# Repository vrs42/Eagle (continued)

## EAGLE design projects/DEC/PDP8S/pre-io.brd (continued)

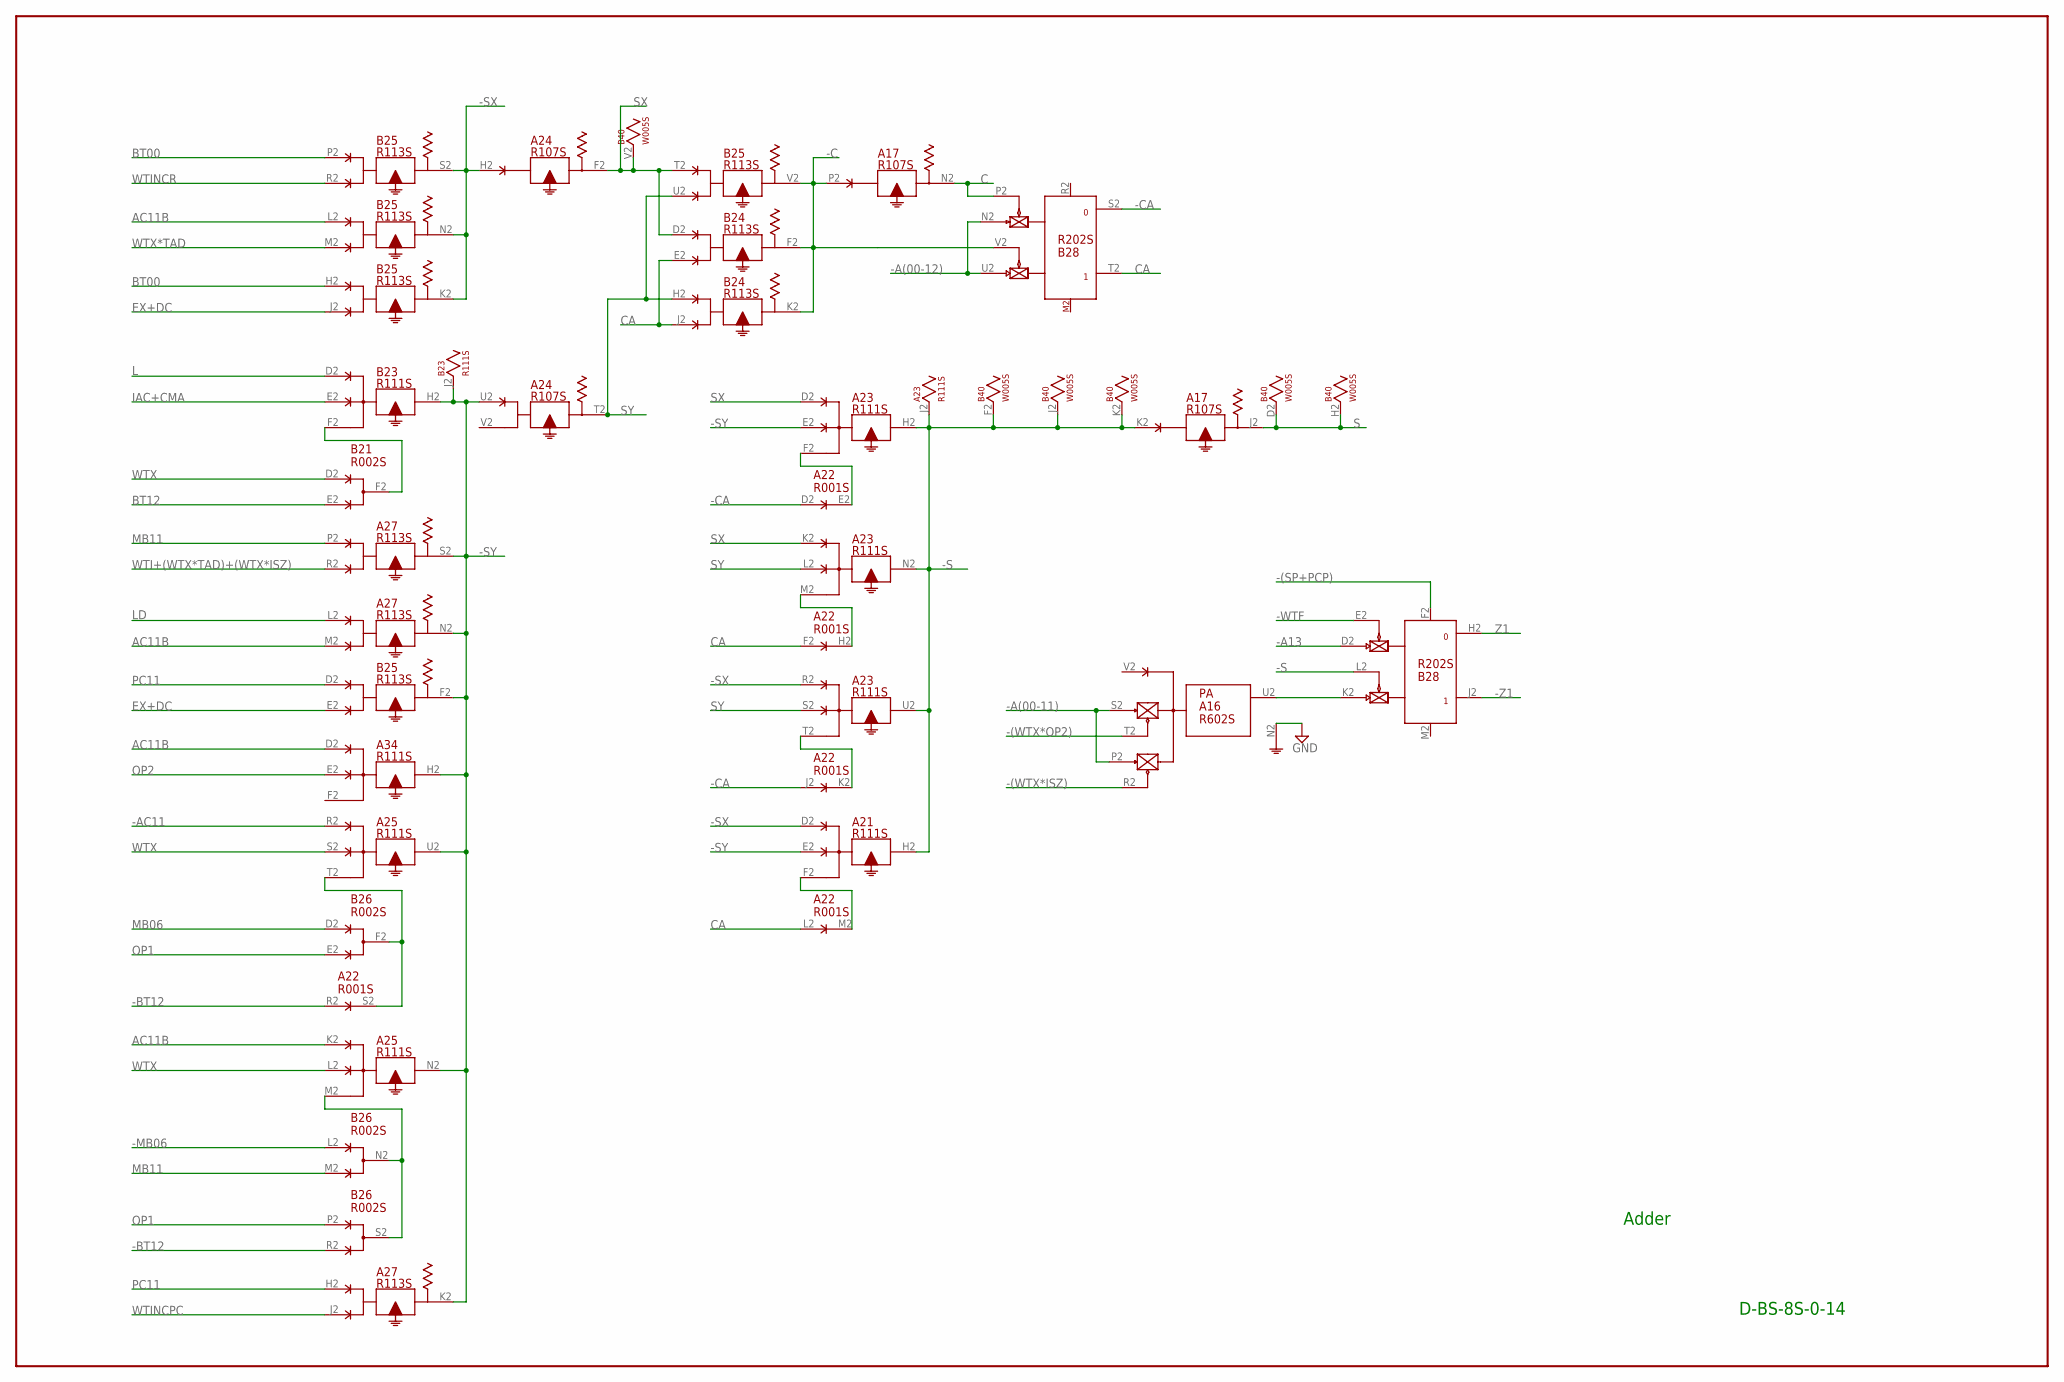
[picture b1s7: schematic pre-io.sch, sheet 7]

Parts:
A16: R602S; H807S
A17, A24: R107S; H807S
A21, A23, A25, A34: R111S; H807S
A22: R001S; H807S
A27: R113S; H807S
B21, B26: R002S; H807S
B23: R111S; H807S
B24, B25: R113S; H807S
B28: R202S; H807S
B40: W005S; H807S

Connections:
-15V: A16.B2 (-15V), A17.B2 (-15V), A21.B2 (-15V), A22.B2 (-15V), A23.B2 (-15V), A24.B2 (-15V), A25.B2 (-15V), A27.B2 (-15V), A34.B2 (-15V), B21.B2 (-15V), B23.B2 (-15V), B24.B2 (-15V), B25.B2 (-15V), B26.B2 (-15V), B28.B2 (-15V), B40.B2 (-15V); also elsewhere on the board
-(SP+PCP): B28.F2 (RESET); also elsewhere on the board
-(WTX*ISZ): A16.R2 (F); also elsewhere on the board
-(WTX*OP2): A16.T2 (J); also elsewhere on the board
-A13: B28.D2 (PU0); also elsewhere on the board
-A(00-11): A16.P2 (E), A16.S2 (H); also elsewhere on the board
-A(00-12): B28.N2 (PU0), B28.U2 (PU1); also elsewhere on the board
-AC11: A25.R2
-BT12: A22.R2 (D), B26.R2 (E); also elsewhere on the board
-C: A17.P2, B24.F2, B24.K2, B25.V2, B28.V2 (EN1)
-CA: A22.D2 (D), A22.J2 (D), B28.S2 (0)
-MB06: B26.L2 (D); also elsewhere on the board
-S: A17.K2, A21.H2, A23.H2, A23.J2, A23.N2, A23.U2, B28.L2 (EN1), B40.F2, B40.J2, B40.K2
-SX: A21.D2, A23.R2, A24.H2, B25.K2, B25.N2, B25.S2
-SY: A21.E2, A23.E2, A24.U2, A25.N2, A25.U2, A27.K2, A27.N2, A27.S2, A34.H2, B23.H2, B23.J2, B25.F2
-WTF: B28.E2 (EN0); also elsewhere on the board
-Z1: B28.J2 (1)
AC11B: A25.K2, A27.M2, A34.D2, B25.L2; also elsewhere on the board
BT00: B25.H2, B25.P2; also elsewhere on the board
BT12: B21.E2 (E)
C: A17.N2, B28.P2 (EN0)
CA: A22.F2 (D), A22.L2 (D), B24.E2, B24.J2, B28.T2 (1)
EX+DC: B25.E2, B25.J2; also elsewhere on the board
GND: A16.C2 (GND), A16.N2 (C), A17.C2 (GND), A21.C2 (GND), A22.C2 (GND), A23.C2 (GND), A24.C2 (GND), A25.C2 (GND), A27.C2 (GND), A34.C2 (GND), B21.C2 (GND), B23.C2 (GND), B24.C2 (GND), B25.C2 (GND), B26.C2 (GND), B28.C2 (GND), B40.C2 (GND); also elsewhere on the board
IAC+CMA: B23.E2; also elsewhere on the board
L: B23.D2; also elsewhere on the board
LD: A27.L2; also elsewhere on the board
MB06: B26.D2 (D); also elsewhere on the board
MB11: A27.P2, B26.M2 (E); also elsewhere on the board
unnamed: B21.F2 (F), B23.F2
unnamed: A16.U2 (K), B28.K2 (PU1)
unnamed: A22.S2 (E), A25.T2, B26.F2 (F)
unnamed: A22.E2 (E), A23.F2
unnamed: A25.M2, B26.N2 (F), B26.S2 (F)
unnamed: A22.H2 (E), A23.M2
unnamed: A22.K2 (E), A23.T2
unnamed: A21.F2, A22.M2 (E)
OP1: B26.E2 (E), B26.P2 (D); also elsewhere on the board
OP2: A34.E2; also elsewhere on the board
PC11: A27.H2, B25.D2; also elsewhere on the board
S: A17.J2, B40.D2, B40.H2; also elsewhere on the board
SX: A23.D2, A23.K2, A24.F2, B24.D2, B25.T2, B40.V2
SY: A23.L2, A23.S2, A24.T2, B24.H2, B25.U2
VCC: A16.A2 (VCC), A17.A2 (VCC), A21.A2 (VCC), A22.A2 (VCC), A23.A2 (VCC), A24.A2 (VCC), A25.A2 (VCC), A27.A2 (VCC), A34.A2 (VCC), B21.A2 (VCC), B23.A2 (VCC), B24.A2 (VCC), B25.A2 (VCC), B26.A2 (VCC), B28.A2 (VCC), B40.A2 (VCC); also elsewhere on the board
WTI+(WTX*TAD)+(WTX*ISZ): A27.R2; also elsewhere on the board
WTINCPC: A27.J2
WTINCR: B25.R2
WTX: A25.L2, A25.S2, B21.D2 (D); also elsewhere on the board
WTX*TAD: B25.M2; also elsewhere on the board
Z1: B28.H2 (0); also elsewhere on the board

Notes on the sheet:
D-BS-8S-0-14
Adder

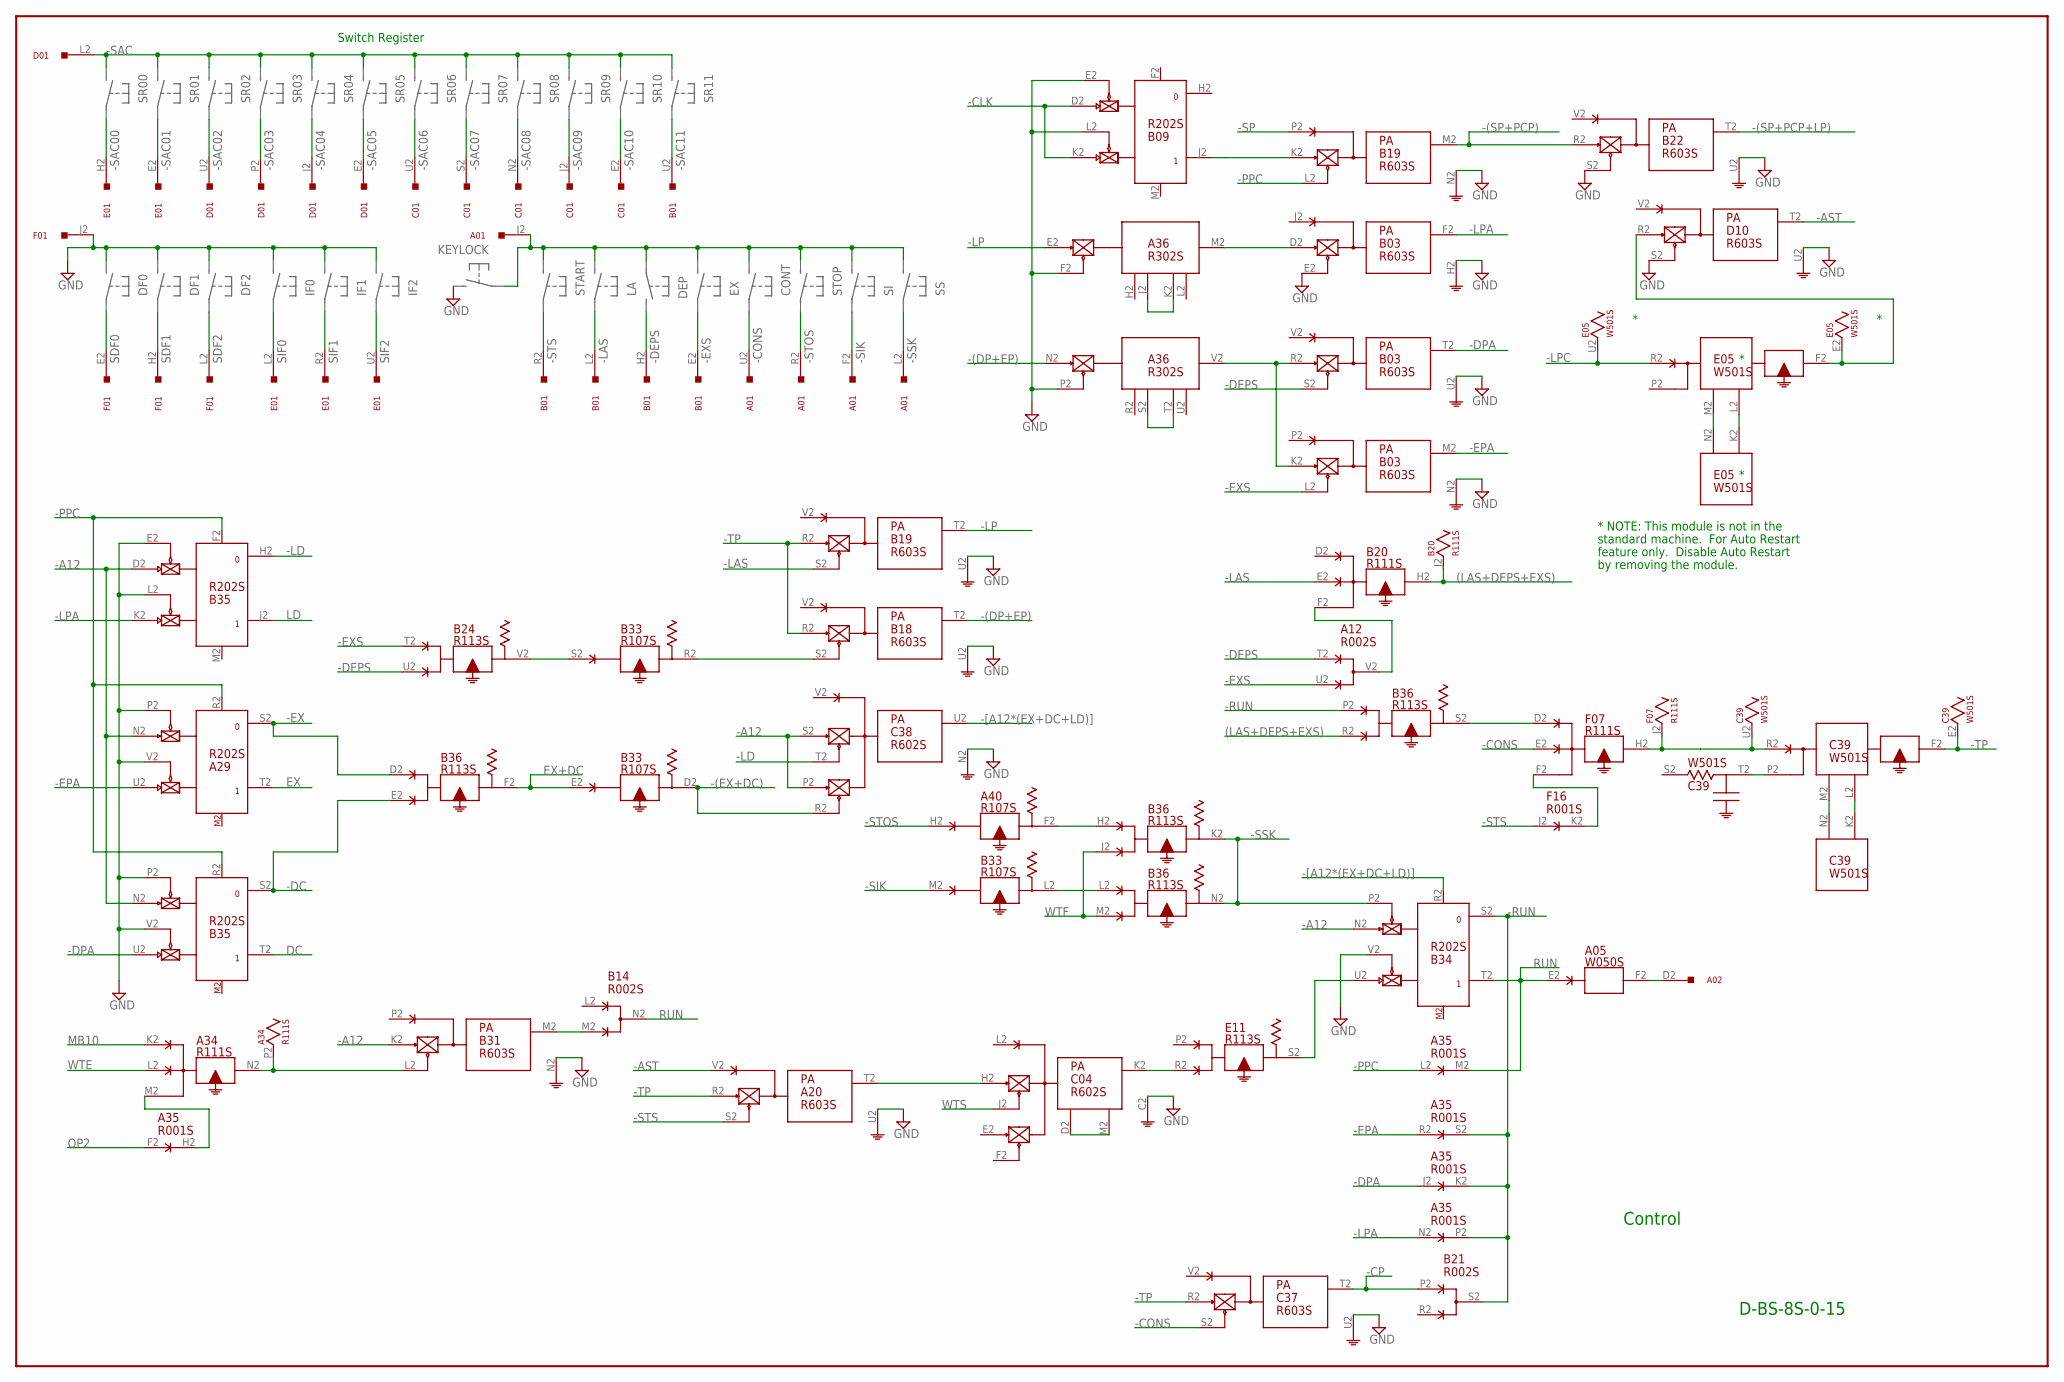
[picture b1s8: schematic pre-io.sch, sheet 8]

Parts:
A01, A02: W023S; H807S
A05: W050S; H807S
A12: R002S; H807S
A20: R603S; H807S
A29: R202S; H807S
A34: R111S; H807S
A35: R001S; H807S
A36: R302S; H807S
A40: R107S; H807S
B01: W023S; H807S
B03, B18, B19, B22, B31: R603S; H807S
B09, B34, B35: R202S; H807S
B14, B21: R002S; H807S
B20: R111S; H807S
B24, B36: R113S; H807S
B33: R107S; H807S
C01: W023S; H807S
C04, C38: R602S; H807S
C37: R603S; H807S
C39: W501S; H807S
D01: W023S; H807S
D10: R603S; H807S
E01: W023S; H807S
E05: W501S; H807S
E11: R113S; H807S
F01: W023S; H807S
F07: R111S; H807S
F16: R001S; H807S

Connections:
(LAS+DEPS+EXS): B20.H2, B20.J2, B36.R2
-15V: A05.B2 (-15V), A12.B2 (-15V), A20.B2 (-15V), A29.B2 (-15V), A34.B2 (-15V), A35.B2 (-15V), A36.B2 (-15V), A40.B2 (-15V), B03.B2 (-15V), B09.B2 (-15V), B14.B2 (-15V), B18.B2 (-15V), B19.B2 (-15V), B20.B2 (-15V), B21.B2 (-15V), B22.B2 (-15V), B24.B2 (-15V), B31.B2 (-15V), B33.B2 (-15V), B34.B2 (-15V), B35.B2 (-15V), B36.B2 (-15V), C04.B2 (-15V), C37.B2 (-15V), C38.B2 (-15V), C39.B2 (-15V), D10.B2 (-15V), E05.B2 (-15V), E11.B2 (-15V), F07.B2 (-15V), F16.B2 (-15V); also elsewhere on the board
-(DP+EP): A36.N2 (E), B18.T2 (O); also elsewhere on the board
-(EX+DC): B33.D2, C38.R2 (F); also elsewhere on the board
-(SP+PCP): B19.M2 (O), B22.R2 (PU0); also elsewhere on the board
-(SP+PCP+LP): B22.T2 (O); also elsewhere on the board
-A12: A29.N2 (PU0), B31.K2 (PU0), B34.N2 (PU0), B35.D2 (PU0), B35.N2 (PU0), C38.P2 (E), C38.S2 (H); also elsewhere on the board
-AST: A20.V2, D10.T2 (O)
-CLK: B09.D2 (PU0), B09.K2 (PU1)
-CONS: A01.U2, C37.S2 (EN0), F07.E2
-CP: B21.P2 (D), C37.T2 (O)
-DC: B35.S2 (0), B36.E2; also elsewhere on the board
-DEPS: A12.T2 (D), B01.H2, B03.S2 (EN0), B24.U2
-DPA: A35.J2 (D), B03.T2 (O), B35.U2 (PU1); also elsewhere on the board
-EPA: A29.U2 (PU1), A35.R2 (D), B03.M2 (O); also elsewhere on the board
-EX: A29.S2 (0), B36.D2; also elsewhere on the board
-EXS: A12.U2 (E), B01.E2, B03.L2 (EN0), B24.T2
-LAS: B01.L2, B19.S2 (EN0), B20.E2
-LD: B35.H2 (0), C38.T2 (J); also elsewhere on the board
-LP: A36.E2 (E), B19.T2 (O); also elsewhere on the board
-LPA: A35.N2 (D), B03.F2 (O), B35.K2 (PU1); also elsewhere on the board
-LPC: E05.R2 (R), E05.U2
-PPC: A29.R2 (RESET), A35.L2 (D), B19.L2 (EN0), B35.F2 (RESET), B35.R2 (RESET); also elsewhere on the board
-RUN: A35.K2 (E), A35.P2 (E), A35.S2 (E), B21.S2 (F), B34.S2 (0), B36.P2; also elsewhere on the board
-SAC: D01.L2; also elsewhere on the board
-SAC00: E01.H2
-SAC01: E01.E2
-SAC02: D01.U2
-SAC03: D01.P2
-SAC04: D01.J2
-SAC05: D01.E2
-SAC06: C01.U2
-SAC07: C01.S2
-SAC08: C01.N2
-SAC09: C01.J2
-SAC10: C01.E2
-SAC11: B01.U2
-SIK: A01.F2, B33.M2
-SP: B19.P2; also elsewhere on the board
-SSK: A01.L2, B34.P2 (EN0), B36.K2, B36.N2
-STOS: A01.R2, A40.H2
-STS: A20.S2 (EN0), B01.R2, F16.J2 (D)
-TP: A20.R2 (PU0), B18.R2 (PU0), B19.R2 (PU0), C37.R2 (PU0), C39.E2, C39.F2 (F)
-[A12*(EX+DC+LD)]: B34.R2 (RESET), C38.U2 (K); also elsewhere on the board
DC: B35.T2 (1); also elsewhere on the board
EX: A29.T2 (1)
EX+DC: B33.E2, B36.F2; also elsewhere on the board
GND: A05.C2 (GND), A12.C2 (GND), A20.C2 (GND), A20.U2 (G), A29.C2 (GND), A29.P2 (EN0), A29.V2 (EN1), A34.C2 (GND), A35.C2 (GND), A36.C2 (GND), A36.F2 (F), A36.P2 (F), A40.C2 (GND), B03.C2 (GND), B03.E2 (EN0), B03.H2 (G), B03.N2 (G), B03.U2 (G), B09.C2 (GND), B09.E2 (EN0), B09.L2 (EN1), B14.C2 (GND), B18.C2 (GND), B18.U2 (G), B19.C2 (GND), B19.N2 (G), B19.U2 (G), B20.C2 (GND), B21.C2 (GND), B22.C2 (GND), B22.S2 (EN0), B22.U2 (G), B24.C2 (GND), B31.C2 (GND), B31.N2 (G), B33.C2 (GND), B34.C2 (GND), B34.V2 (EN1), B35.C2 (GND), B35.E2 (EN0), B35.L2 (EN1), B35.P2 (EN0), B35.V2 (EN1), B36.C2 (GND), C04.C2 (GND), C37.C2 (GND), C37.U2 (G), C38.C2 (GND), C38.N2 (C), C39.C2 (GND), C39.V2 (GND), D10.C2 (GND), D10.S2 (EN0), D10.U2 (G), E05.C2 (GND), E05.V2 (GND), E11.C2 (GND), F01.J2, F07.C2 (GND), F16.C2 (GND); also elsewhere on the board
LD: B35.J2 (1); also elsewhere on the board
MB10: A34.K2; also elsewhere on the board
unnamed: A34.M2, A35.H2 (E)
unnamed: A34.N2, A34.P2, B31.L2 (EN0)
unnamed: B14.M2 (E), B31.M2 (O)
unnamed: B24.V2, B33.S2
unnamed: B34.U2 (PU1), E11.S2
unnamed: B18.S2 (EN0), B33.R2
unnamed: A36.S2 (J), A36.T2 (K)
unnamed: A36.J2 (J), A36.K2 (K)
unnamed: E05.M2 (M), E05.N2 (N)
unnamed: E05.K2 (K), E05.L2 (L)
unnamed: B09.J2 (1), B19.K2 (PU0)
unnamed: D10.R2 (PU0), E05.E2, E05.F2 (F)
unnamed: A36.M2 (M), B03.D2 (PU0)
unnamed: A36.V2 (M), B03.K2 (PU0), B03.R2 (PU0)
unnamed: A12.V2 (F), B20.F2
unnamed: C39.M2 (M), C39.N2 (N)
unnamed: C39.K2 (K), C39.L2 (L)
unnamed: C39.P2, C39.T2 (T)
unnamed: C39.R2 (R), C39.U2, F07.H2, F07.J2
unnamed: B36.S2, F07.D2
unnamed: F07.F2, F16.K2 (E)
unnamed: A02.D2, A05.F2
unnamed: C04.K2 (K), E11.R2
unnamed: B33.L2, B36.L2
unnamed: A40.F2, B36.H2
unnamed: C04.D2 (D), C04.M2 (M)
unnamed: A20.T2 (O), C04.H2 (H)
OP2: A35.F2 (D); also elsewhere on the board
RUN: A05.E2, A35.M2 (E), B14.N2 (F), B34.T2 (1)
SDF0: F01.E2
SDF1: F01.H2
SDF2: F01.L2
SIF0: E01.L2
SIF1: E01.R2
SIF2: E01.U2
VCC: A05.A2 (VCC), A12.A2 (VCC), A20.A2 (VCC), A29.A2 (VCC), A34.A2 (VCC), A35.A2 (VCC), A36.A2 (VCC), A40.A2 (VCC), B03.A2 (VCC), B09.A2 (VCC), B14.A2 (VCC), B18.A2 (VCC), B19.A2 (VCC), B20.A2 (VCC), B21.A2 (VCC), B22.A2 (VCC), B24.A2 (VCC), B31.A2 (VCC), B33.A2 (VCC), B34.A2 (VCC), B35.A2 (VCC), B36.A2 (VCC), C04.A2 (VCC), C37.A2 (VCC), C38.A2 (VCC), C39.A2 (VCC), D10.A2 (VCC), E05.A2 (VCC), E11.A2 (VCC), F07.A2 (VCC), F16.A2 (VCC); also elsewhere on the board
WTE: A34.L2; also elsewhere on the board
WTF: B36.J2, B36.M2; also elsewhere on the board
WTS: C04.J2 (J); also elsewhere on the board

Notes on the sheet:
D-BS-8S-0-15
Control
Switch Register
* NOTE: This module is not in the
standard machine. For Auto Restart
feature only. Disable Auto Restart
by removing the module.

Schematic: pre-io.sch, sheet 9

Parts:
A02: W023S; H807S
A06, A07: W050S; H807S
A18: R107S; H807S
B02: W023S; H807S
B13, B20: R111S; H807S
B21: R002S; H807S
B22: R603S; H807S
C11: R001S; H807S
C37: R603S; H807S
D17: R151S; H807S
D19, D20: R202S; H807S
E09, E10, E11, E13: R113S; H807S
F13, F18, F19, F20: R107S; H807S
F14: R113S; H807S
F15, F17: R111S; H807S
F16: R001S; H807S

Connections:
(ISZ*Z1)+JMS+(OP+IOT)*SKP: F15.N2, F15.P2, F19.M2
-15V: A06.B2 (-15V), A07.B2 (-15V), A18.B2 (-15V), B13.B2 (-15V), B20.B2 (-15V), B21.B2 (-15V), B22.B2 (-15V), C11.B2 (-15V), C37.B2 (-15V), D17.B2 (-15V), D19.B2 (-15V), D20.B2 (-15V), E09.B2 (-15V), E10.B2 (-15V), E11.B2 (-15V), E13.B2 (-15V), F13.B2 (-15V), F14.B2 (-15V), F15.B2 (-15V), F16.B2 (-15V), F17.B2 (-15V), F18.B2 (-15V), F19.B2 (-15V), F20.B2 (-15V); also elsewhere on the board
-(IAC+CMA): B21.H2 (D), E10.R2, F19.T2
-(ISZ*Z1): E11.V2, F16.N2 (D)
-(OP+IOT): E11.M2, F13.R2; also elsewhere on the board
-(SP+PCP+LP): C37.P2; also elsewhere on the board
-A00: C37.K2 (PU0); also elsewhere on the board
-A1: E09.T2; also elsewhere on the board
-A(00-11): B22.K2 (PU0); also elsewhere on the board
-AND: B13.K2, B20.K2, D17.M2 (M), F15.R2, F20.E2
-CLL: E13.S2, F19.P2; also elsewhere on the board
-CMA: F14.K2, F14.M2
-CML: E13.V2, F13.E2; also elsewhere on the board
-DCA: B20.S2, B21.M2 (E), D17.R2 (R), F20.M2
-IAC: F14.F2, F14.L2
-IOT: D17.U2 (U), E11.J2, F20.U2
-IR00: D17.J2 (J), D20.H2 (0), D20.V2 (EN1)
-IR01: D17.E2 (E), D19.L2 (EN1), D20.S2 (0)
-IR02: D17.K2 (K), D19.H2 (0), D19.V2 (EN1)
-IR03: A18.U2, D19.S2 (0), E10.E2; also elsewhere on the board
-IRCLR: C37.M2 (O), D19.F2 (RESET), D19.R2 (RESET), D20.F2 (RESET), D20.R2 (RESET)
-IRSH: B22.M2 (O), D19.D2 (PU0), D19.K2 (PU1), D19.N2 (PU0), D19.U2 (PU1), D20.D2 (PU0), D20.K2 (PU1), D20.N2 (PU0), D20.U2 (PU1)
-ISZ: B21.U2 (E), C11.T2 (D), D17.P2, F20.K2
-JMP: D17.T2 (T), E10.M2, F16.R2 (D), F20.S2
-JMS: B20.R2, D17.S2 (S), F15.L2, F20.P2
-MB10: E09.D2; also elsewhere on the board
-MB11: D20.L2 (EN1); also elsewhere on the board
-OP1: E10.F2, F16.T2 (D), F18.K2
-OP2: B21.J2 (E), B21.T2 (D), E09.M2, E11.F2, F18.P2
-OPR: D17.V2 (V), E11.H2, F19.K2; also elsewhere on the board
-ROTL: B21.L2 (D), F17.N2, F17.P2, F17.S2
-ROTR: F17.H2, F17.J2, F17.R2, F19.S2; also elsewhere on the board
-TAD: B13.L2, B20.L2, D17.N2 (N), E10.P2, F15.S2, F16.L2 (D), F20.H2
-WTB: C37.L2 (EN0); also elsewhere on the board
-WTF: B22.L2 (EN0); also elsewhere on the board
-[(ISZ*Z1)+JMS+(OP+IOT)*SKP+JMP]: F19.F2
A1: E09.P2; also elsewhere on the board
AND: A06.H2, F20.D2
AND+TAD+DCA+IAC+CMA+ROTL+OP2: B20.N2, B20.P2
AND+TAD+ISZ: B13.N2, B13.P2; also elsewhere on the board
AND+TAD+OP1+JMP: F15.U2, F15.V2; also elsewhere on the board
BT00: E09.E2, E09.H2; also elsewhere on the board
CLL: F19.N2; also elsewhere on the board
CML: F13.D2; also elsewhere on the board
DCA: A06.P2, F20.L2; also elsewhere on the board
EX+DC: D17.D2 (D); also elsewhere on the board
GND: A06.C2 (GND), A07.C2 (GND), A18.C2 (GND), B13.C2 (GND), B20.C2 (GND), B21.C2 (GND), B22.C2 (GND), B22.N2 (G), C11.C2 (GND), C37.C2 (GND), C37.N2 (G), D17.C2 (GND), D19.C2 (GND), D20.C2 (GND), E09.C2 (GND), E10.C2 (GND), E11.C2 (GND), E13.C2 (GND), F13.C2 (GND), F14.C2 (GND), F15.C2 (GND), F16.C2 (GND), F17.C2 (GND), F18.C2 (GND), F19.C2 (GND), F20.C2 (GND); also elsewhere on the board
IAC+CMA: F14.N2, F19.U2; also elsewhere on the board
IOT: A07.E2, F20.T2
IR00: D17.H2 (H), D20.J2 (1), D20.P2 (EN0)
IR01: D17.F2 (F), D19.E2 (EN0), D20.T2 (1)
IR02: D17.L2 (L), D19.J2 (1), D19.P2 (EN0)
IR03: D19.T2 (1), E11.D2; also elsewhere on the board
IR03*-A1: F13.J2; also elsewhere on the board
IR03*A1: F13.N2; also elsewhere on the board
IR03B: A18.T2, E09.R2, E09.U2
ISZ: A06.M2, E11.T2, F20.J2
ISZ+DCA+JMS: F18.T2
JMP: A06.U2, F20.R2; also elsewhere on the board
JMS: A06.S2, F20.N2; also elsewhere on the board
JMS+DCA+ISZ+OP2: B20.U2, B20.V2, E09.L2
MB05: E13.P2; also elsewhere on the board
MB06: F14.J2; also elsewhere on the board
MB07: E13.T2; also elsewhere on the board
MB08: F17.E2; also elsewhere on the board
MB09: F17.L2; also elsewhere on the board
MB11: D20.E2 (EN0), F14.E2; also elsewhere on the board
unnamed: A02.V2, A07.F2
unnamed: A02.N2, A06.J2
unnamed: F15.T2, F16.S2 (E), F16.U2 (E)
unnamed: B20.M2, B21.K2 (F), B21.N2 (F)
unnamed: B13.M2, C11.U2 (E)
unnamed: A02.P2, A06.L2
unnamed: E09.S2, F13.P2
unnamed: F16.M2 (E), F17.T2
unnamed: E09.V2, F13.K2
unnamed: A02.R2, A06.N2
unnamed: F16.E2 (E), F17.F2
unnamed: F16.H2 (E), F17.M2
unnamed: A02.U2, A06.V2
unnamed: E09.F2, F16.D2 (D)
unnamed: E09.K2, F16.F2 (D)
unnamed: E10.L2, F19.L2
unnamed: A07.J2, B02.D2
unnamed: E11.N2, F15.K2
unnamed: E10.N2, F19.H2
unnamed: B20.T2, B21.V2 (F)
unnamed: A02.T2, A06.T2
unnamed: F15.M2, F16.P2 (E)
unnamed: A02.S2, A06.R2
unnamed: E09.N2, F18.U2
OP1: E13.R2, E13.U2, F14.D2, F14.H2, F17.D2, F17.K2, F18.J2; also elsewhere on the board
OP2: F18.N2; also elsewhere on the board
OP+IOT: E11.K2, F13.S2
OPR: A07.H2, E10.D2, E11.E2, F19.J2
ROTR: F19.R2; also elsewhere on the board
ROTR+ROTL+TAD: F17.U2, F17.V2; also elsewhere on the board
SKP: E11.L2; also elsewhere on the board
TAD: A06.K2, F20.F2; also elsewhere on the board
TAD+IAC+CMA: E10.S2; also elsewhere on the board
VCC: A06.A2 (VCC), A07.A2 (VCC), A18.A2 (VCC), B13.A2 (VCC), B20.A2 (VCC), B21.A2 (VCC), B22.A2 (VCC), C11.A2 (VCC), C37.A2 (VCC), D17.A2 (VCC), D19.A2 (VCC), D20.A2 (VCC), E09.A2 (VCC), E10.A2 (VCC), E11.A2 (VCC), E13.A2 (VCC), F13.A2 (VCC), F14.A2 (VCC), F15.A2 (VCC), F16.A2 (VCC), F17.A2 (VCC), F18.A2 (VCC), F19.A2 (VCC), F20.A2 (VCC); also elsewhere on the board
Z1: E11.U2; also elsewhere on the board

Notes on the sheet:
D-BS-8S-0-16
Instruction Register

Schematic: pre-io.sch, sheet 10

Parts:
D06A: R113S; H807S
F22A: W005S; H807S

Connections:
-15V: D06A.B2 (-15V), F22A.B2 (-15V); also elsewhere on the board
GND: D06A.C2 (GND), F22A.C2 (GND); also elsewhere on the board
VCC: D06A.A2 (VCC), F22A.A2 (VCC); also elsewhere on the board

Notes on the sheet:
D-BS-8S-0-17
In-Out

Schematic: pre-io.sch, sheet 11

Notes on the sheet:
D-BS-8S-0-19
Program Counter

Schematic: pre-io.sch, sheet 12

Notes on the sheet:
D-BS-8S-0-20
Accumulator

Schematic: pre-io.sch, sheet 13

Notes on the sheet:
D-BS-8S-0-22
Memory Control

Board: 4 copper layers, 225 parts (0 on the bottom side), 495 nets, no tracks yet.

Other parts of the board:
U$1, U$2, U$3, U$4, U$5, U$6, U$7, U$8, U$9, U$10, U$11, U$12, U$13, U$14, U$15, U$16, U$17, U$18, U$19, U$20, U$21, U$22, U$23, U$24, U$25, U$26, U$27, U$28, U$29, U$30: CBLOCK

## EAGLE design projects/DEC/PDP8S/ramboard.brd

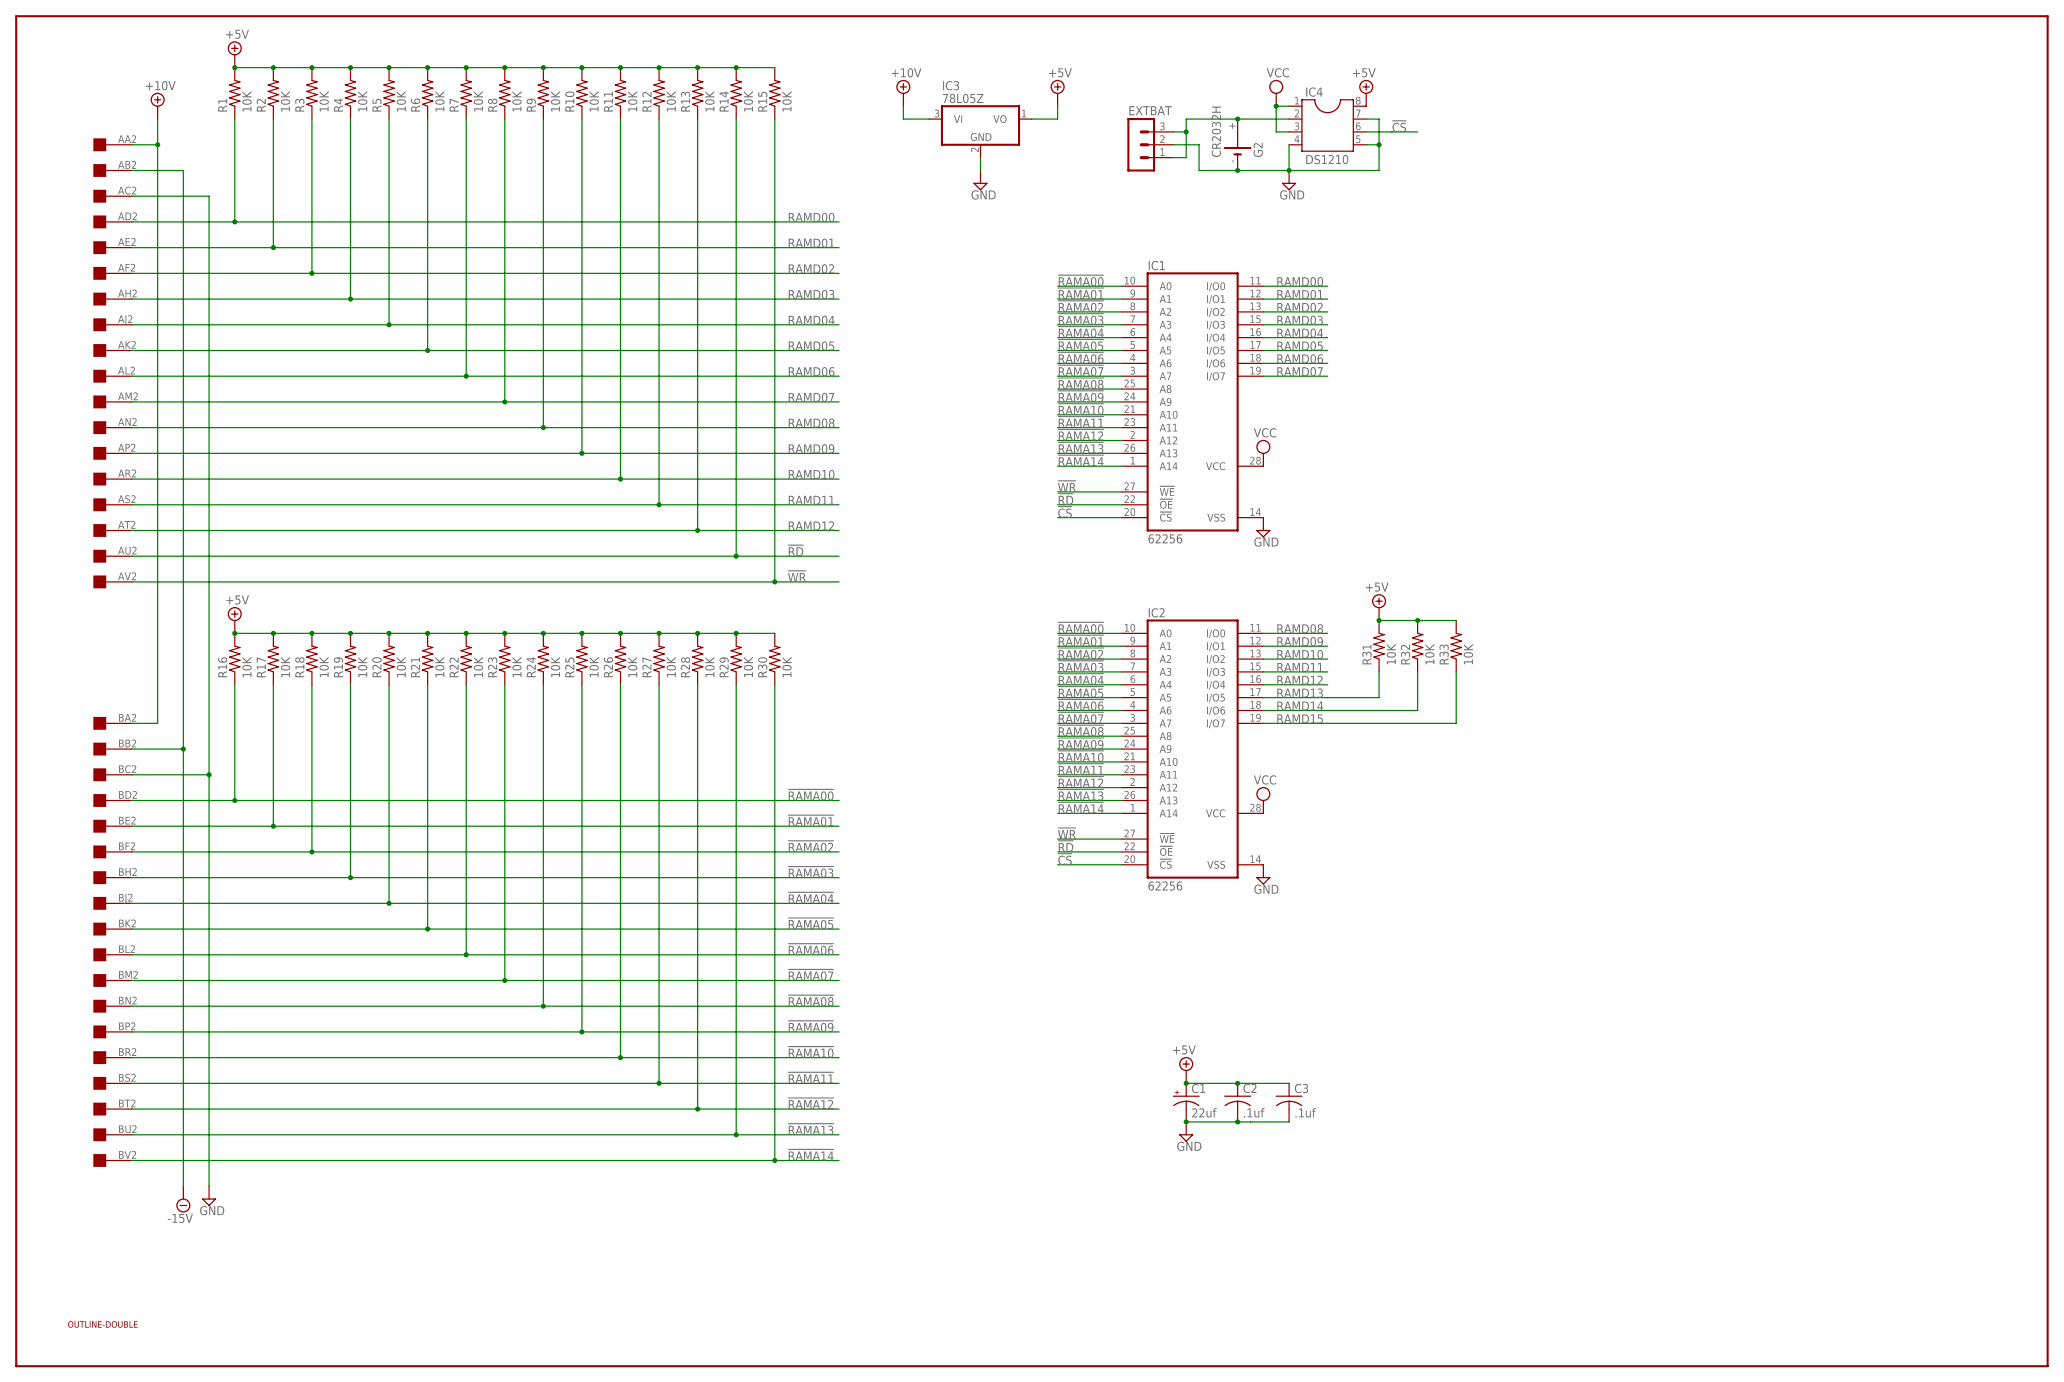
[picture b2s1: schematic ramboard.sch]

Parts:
C1: 22uf; E22-6
C2, C3: .1uf; C050-025X075
EXTBAT: MA03-1
G2: CR2032H
IC1, IC2: 62256; DIL28-6
IC3: 78L05Z; TO92
IC4: DS1210; SOCKET-08
R1, R2, R3, R4, R5, R6, R7, R8, R9, R10, R11, R12, R13, R14, R15, R16, R17, R18, R19, R20, R21, R22, R23, R24, R25, R26, R27, R28, R29, R30, R31, R32, R33: 10K; 0207/10
U$1: OUTLINE-DOUBLE; DOUBLE
U$2: DOUBLE; EDGE-CON4

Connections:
!CS: IC1.20 (!CS), IC2.20 (!CS), IC4.6
!RAMA00: IC1.10 (A0), IC2.10 (A0), R16.1, U$2.BD2
!RAMA01: IC1.9 (A1), IC2.9 (A1), R17.1, U$2.BE2
!RAMA02: IC1.8 (A2), IC2.8 (A2), R18.1, U$2.BF2
!RAMA03: IC1.7 (A3), IC2.7 (A3), R19.1, U$2.BH2
!RAMA04: IC1.6 (A4), IC2.6 (A4), R20.1, U$2.BJ2
!RAMA05: IC1.5 (A5), IC2.5 (A5), R21.1, U$2.BK2
!RAMA06: IC1.4 (A6), IC2.4 (A6), R22.1, U$2.BL2
!RAMA07: IC1.3 (A7), IC2.3 (A7), R23.1, U$2.BM2
!RAMA08: IC1.25 (A8), IC2.25 (A8), R24.1, U$2.BN2
!RAMA09: IC1.24 (A9), IC2.24 (A9), R25.1, U$2.BP2
!RAMA10: IC1.21 (A10), IC2.21 (A10), R26.1, U$2.BR2
!RAMA11: IC1.23 (A11), IC2.23 (A11), R27.1, U$2.BS2
!RAMA12: IC1.2 (A12), IC2.2 (A12), R28.1, U$2.BT2
!RAMA13: IC1.26 (A13), IC2.26 (A13), R29.1, U$2.BU2
!RAMA14: IC1.1 (A14), IC2.1 (A14), R30.1, U$2.BV2
!RD: IC1.22 (!OE), IC2.22 (!OE), R14.1, U$2.AU2
!WR: IC1.27 (!WE), IC2.27 (!WE), R15.1, U$2.AV2
+5V: C1.+, C2.1, C3.1, IC3.1 (VO), IC4.8, R1.2, R2.2, R3.2, R4.2, R5.2, R6.2, R7.2, R8.2, R9.2, R10.2, R11.2, R12.2, R13.2, R14.2, R15.2, R16.2, R17.2, R18.2, R19.2, R20.2, R21.2, R22.2, R23.2, R24.2, R25.2, R26.2, R27.2, R28.2, R29.2, R30.2, R31.2, R32.2, R33.2
+10V: IC3.3 (VI), U$2.AA2, U$2.BA2
-15V: U$2.AB2, U$2.BB2
GND: C1.-, C2.2, C3.2, EXTBAT.2, G2.-, IC1.14 (VSS), IC2.14 (VSS), IC3.2 (GND), IC4.4, IC4.5, IC4.7, U$2.AC2, U$2.BC2
unnamed: EXTBAT.1, EXTBAT.3, G2.+, IC4.2
RAMD00: IC1.11 (I/O0), R1.1, U$2.AD2
RAMD01: IC1.12 (I/O1), R2.1, U$2.AE2
RAMD02: IC1.13 (I/O2), R3.1, U$2.AF2
RAMD03: IC1.15 (I/O3), R4.1, U$2.AH2
RAMD04: IC1.16 (I/O4), R5.1, U$2.AJ2
RAMD05: IC1.17 (I/O5), R6.1, U$2.AK2
RAMD06: IC1.18 (I/O6), R7.1, U$2.AL2
RAMD07: IC1.19 (I/O7), R8.1, U$2.AM2
RAMD08: IC2.11 (I/O0), R9.1, U$2.AN2
RAMD09: IC2.12 (I/O1), R10.1, U$2.AP2
RAMD10: IC2.13 (I/O2), R11.1, U$2.AR2
RAMD11: IC2.15 (I/O3), R12.1, U$2.AS2
RAMD12: IC2.16 (I/O4), R13.1, U$2.AT2
RAMD13: IC2.17 (I/O5), R31.1
RAMD14: IC2.18 (I/O6), R32.1
RAMD15: IC2.19 (I/O7), R33.1
VCC: IC1.28 (VCC), IC2.28 (VCC), IC4.1, IC4.3

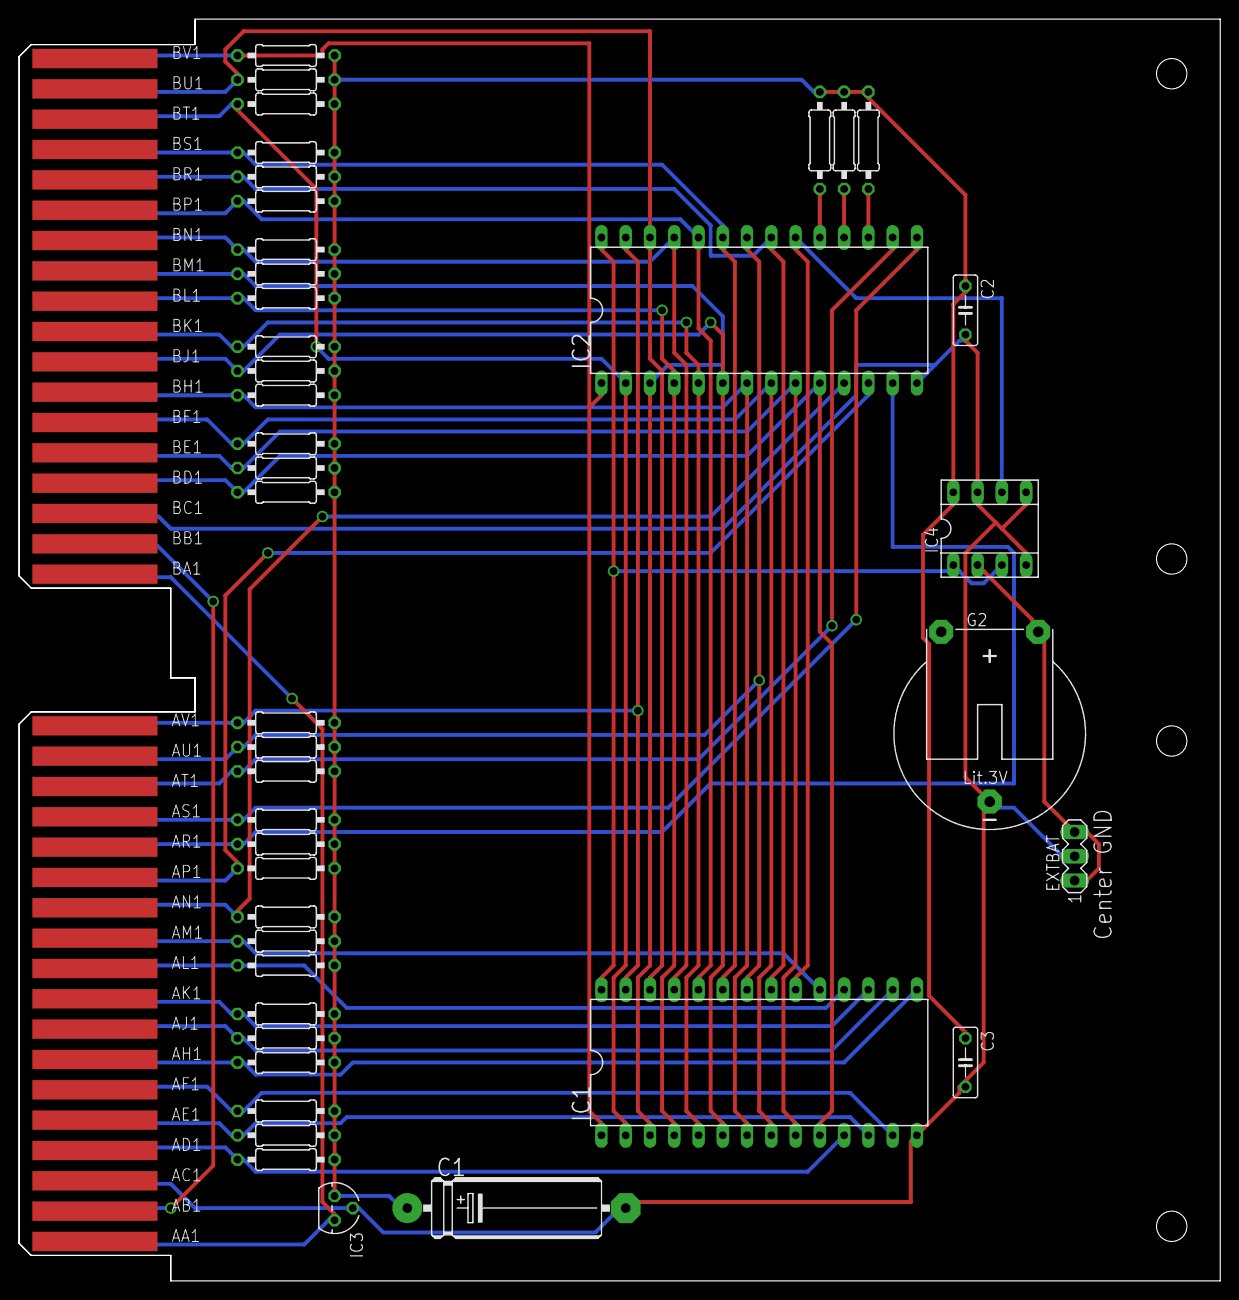
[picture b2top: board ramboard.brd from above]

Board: 2 copper layers, 125.7 x 132.1 mm, 44 parts (0 on the bottom side), 40 nets.

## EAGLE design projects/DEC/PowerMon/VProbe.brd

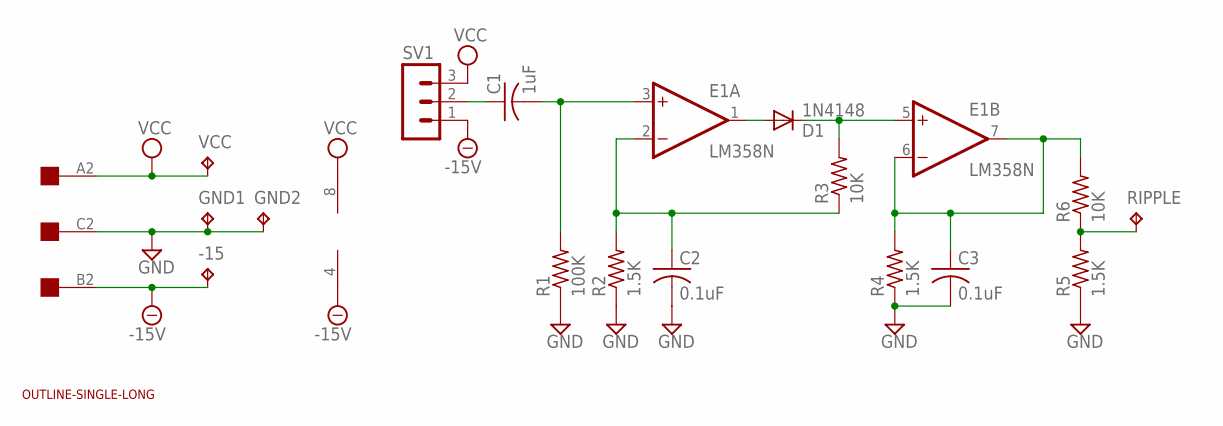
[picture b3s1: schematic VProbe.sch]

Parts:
-15: TPPAD1-13; P1-13
C1: 1uF; C075-032X103
C2, C3: 0.1uF; C075-032X103
D1: 1N4148; DO35-10
E1: LM358N; DIL08
GND1, GND2: TPPAD1-13; P1-13
R1: 100K; 0207/10
R2, R4, R5: 1.5K; 0207/10
R3, R6: 10K; 0207/10
RIPPLE: TPPAD1-13; P1-13
SV1: MA03-1
U$1: EDGE-1; EDGE-CON1
U$2: OUTLINE-SINGLE-LONG; SINGLE-LONG
VCC: TPPAD1-13; P1-13

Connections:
-15V: -15.TP, E1.4 (V-), SV1.1, U$1.B2
GND: C2.2, C3.2, GND1.TP, GND2.TP, R1.1, R2.1, R4.1, R5.1, U$1.C2
unnamed: C1.2, E1.3 (+IN), R1.2
unnamed: D1.A, E1.1 (OUT)
unnamed: C2.1, E1.2 (-IN), R2.2, R3.1
unnamed: C3.1, E1.6 (-IN), E1.7 (OUT), R4.2, R6.2
unnamed: D1.C, E1.5 (+IN), R3.2
unnamed: R5.2, R6.1, RIPPLE.TP
unnamed: C1.1, SV1.2
VCC: E1.8 (V+), SV1.3, U$1.A2, VCC.TP

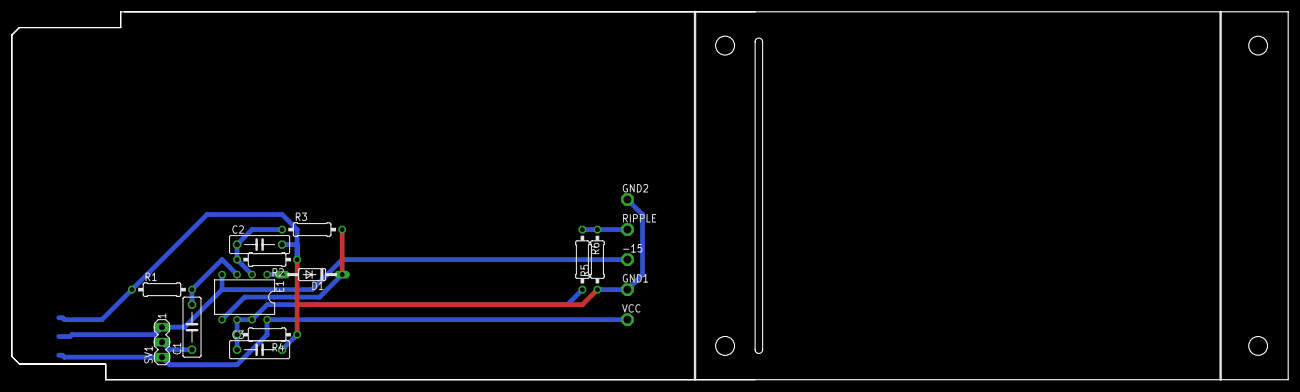
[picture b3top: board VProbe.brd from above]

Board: 2 copper layers, 215.9 x 62.2 mm, 19 parts (0 on the bottom side), 10 nets.
